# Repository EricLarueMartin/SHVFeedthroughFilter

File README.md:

# SHVFeedthroughFilter
Coaxial feedthrough filter that mounts on an SHV bulkhead.

SHV bulkhead connectors on both ends allow mounting the filter such that the body of the filter is on either side of the bulkhead, which may be helpful for space constraints.

Uses commercially available parts to make a high voltage filter that fits on a standard SHV bulkhead connector.
This filter was designed for use biasing cryogenically cooled solid state detectors, which have very low leakage current making high resistance series elements suitable.

Resistors are axial lead able to handle the high voltage while the sides of the resistor body are near ground, such as Ohmite MOX112523*. Though a shorter resistor would work the stray capacitance is important to performance and this model has the lowest stray capacitance at 0.25 pF.

Connector used for protoype was TE Connectivity AMP Connectors 5225059-3, this is out of production and an alternative will become necessary when stocks depleate. The BM61482 from Bracke Manufacturing appears to be a direct replacement. 

Capacitors are 6kV 2225 package, such as Vishay Vitramon HV2225*. Six 2.7 nF capacitors were used for the prototype, but three high capacitance X7R capacitors and three lower capacitance C0G capacitors would likely result in better high frequency performance.

The center piece for the capacitors to solder to is a brass standoff, 6 mm hex diameter and up to 6mm height.

The tube is a 0.686 inch ID brass or copper tube. A 3/4 inch 0.032 inch wall tube is readily available and suitable.

A bleeder resistor on the load side of this filter will result in voltage drop across the series resistors. Bleeder resistors are not required if stored energy is under 10 J. 

The prototype filter used six 2.7 nF capacitors, which will only result in 0.3 J of stored energy at 6 kV. With 100 Mohm series resistors the maximum current the filter can produce is only 60 microamps at 6 kV, which is negligible compared to the ~10 mA requires to produce a dangerous shock. With 0.25 pF of parallel capacitance this high of a resistance isn't effective at frequencies above 10 kHz. 5 Mohm resistors would still limit the current from a shock to ~ 1 mA and performance at power distribution frequencies would still be better than 100 dB.

The cable ground of the recommended connector acts as a guard ring to reduce the effective capacitance between leads of the axial resistors, this stray capacitance dominates filter performance in the GHz range. A guard ring is added using washers for the second stage resistor.

This version includes a second capacitor stage with a pulse line. This allows pulsing through the HV line and also provides source termination at the filter, which can help reduce noise that is picked up on the HV line after the filter.

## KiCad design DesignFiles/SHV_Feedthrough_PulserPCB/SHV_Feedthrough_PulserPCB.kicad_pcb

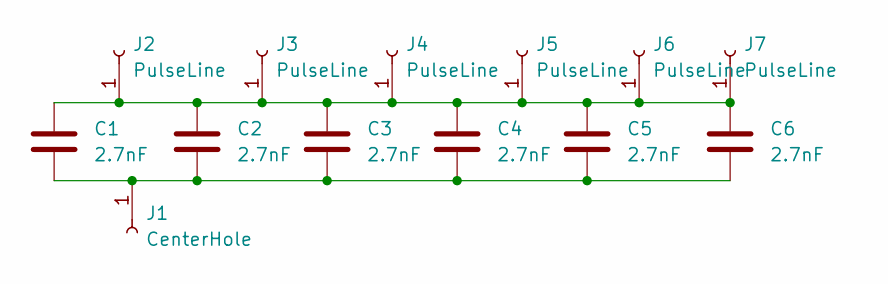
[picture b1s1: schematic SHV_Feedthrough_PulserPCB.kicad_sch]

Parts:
C1, C2, C3, C4, C5, C6: 2.7nF; HV2225SideMount
J1: CenterHole; MountingHole_2.1mm
J2, J3, J4, J5, J6, J7: PulseLine; RG-174MinHole

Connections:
unnamed: C1.1, C2.1, C3.1, C4.1, C5.1, C6.1, J2.1, J3.1, J4.1, J5.1, J6.1, J7.1
unnamed: C1.2, C2.2, C3.2, C4.2, C5.2, C6.2, J1.1

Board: 2 copper layers, 13 parts (0 on the bottom side), 2 nets, no tracks yet.

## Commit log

2022-02-08 Added 3D rendering of design.
2022-02-08 Added jigs.
2022-02-10 Added STLs for jigs, data sheets, and LTspice simulation.
2022-02-11 Started working on instructions.
2022-02-13 Reorganized directory structure. Minor changes to some files.
2022-02-20 Completed first draft of instructions.
2022-02-23 Revised instructions
2022-02-24 Added versions with two SHV jacks and with more common SHV jacks using adapters.
2022-02-25 Data sheet for replacement connector from Bracke Manufacturing.
2022-02-26 Slight modification to capacitor jig. Added multi-body files for 3D printing intended for individual part completion.
2022-02-26 Added construction image of resistor.
2022-02-26 Added images and BM60261.
2022-02-26 Added simulation outputs and 16 grommet individual object completion file for 3D printing.
2022-02-26 Added BM60829 info.
2022-03-03 Photo of prefilter on LEGEND filter
2022-03-03 File to printing 9 jigs one at a time
2022-03-20 Updated Performance
2022-03-21 Added plots used for slides.
2022-06-27 Added second capacitor stage with pulse line.
2022-07-12 Version for LEGEND, with separate grounds for input and filter connected by resistor.
2022-07-12 Removed PCB jig, use resulted in breaking resistors.
2022-07-12 Added design file.
2022-07-13 Added files for printing.
2022-07-13 Modified tube hole position. Small change to end cap design.
2022-08-04 Added more jigs and updated instructions to make assembly easier.
2022-08-04 Added solder recommendations and reformatted parts list.
2022-08-04 Fixed figure clipping issue.
2022-08-09 Modified instructions.
2022-08-11 Updated instructions to include ensuring MIL-STD-348B_CHG-3 conformity.
2022-09-12 Added procedure for cleaning with Acetone
2022-09-12 Corrections to cleaning with 413B-Liquid
2022-09-12 Added slots to pulser board. Updated instructions for cleaning.
2022-09-13 Updated potting and cleaning instructions.
